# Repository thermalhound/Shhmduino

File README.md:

# SHHMduino
SHH&amp;M Arduino Clone

Files required to build the SHHMduino Arduino Clone

Initial upload on 22/01/2016 Rev A - UNTESTED

Update 5/7/2022 - Project no longer supported

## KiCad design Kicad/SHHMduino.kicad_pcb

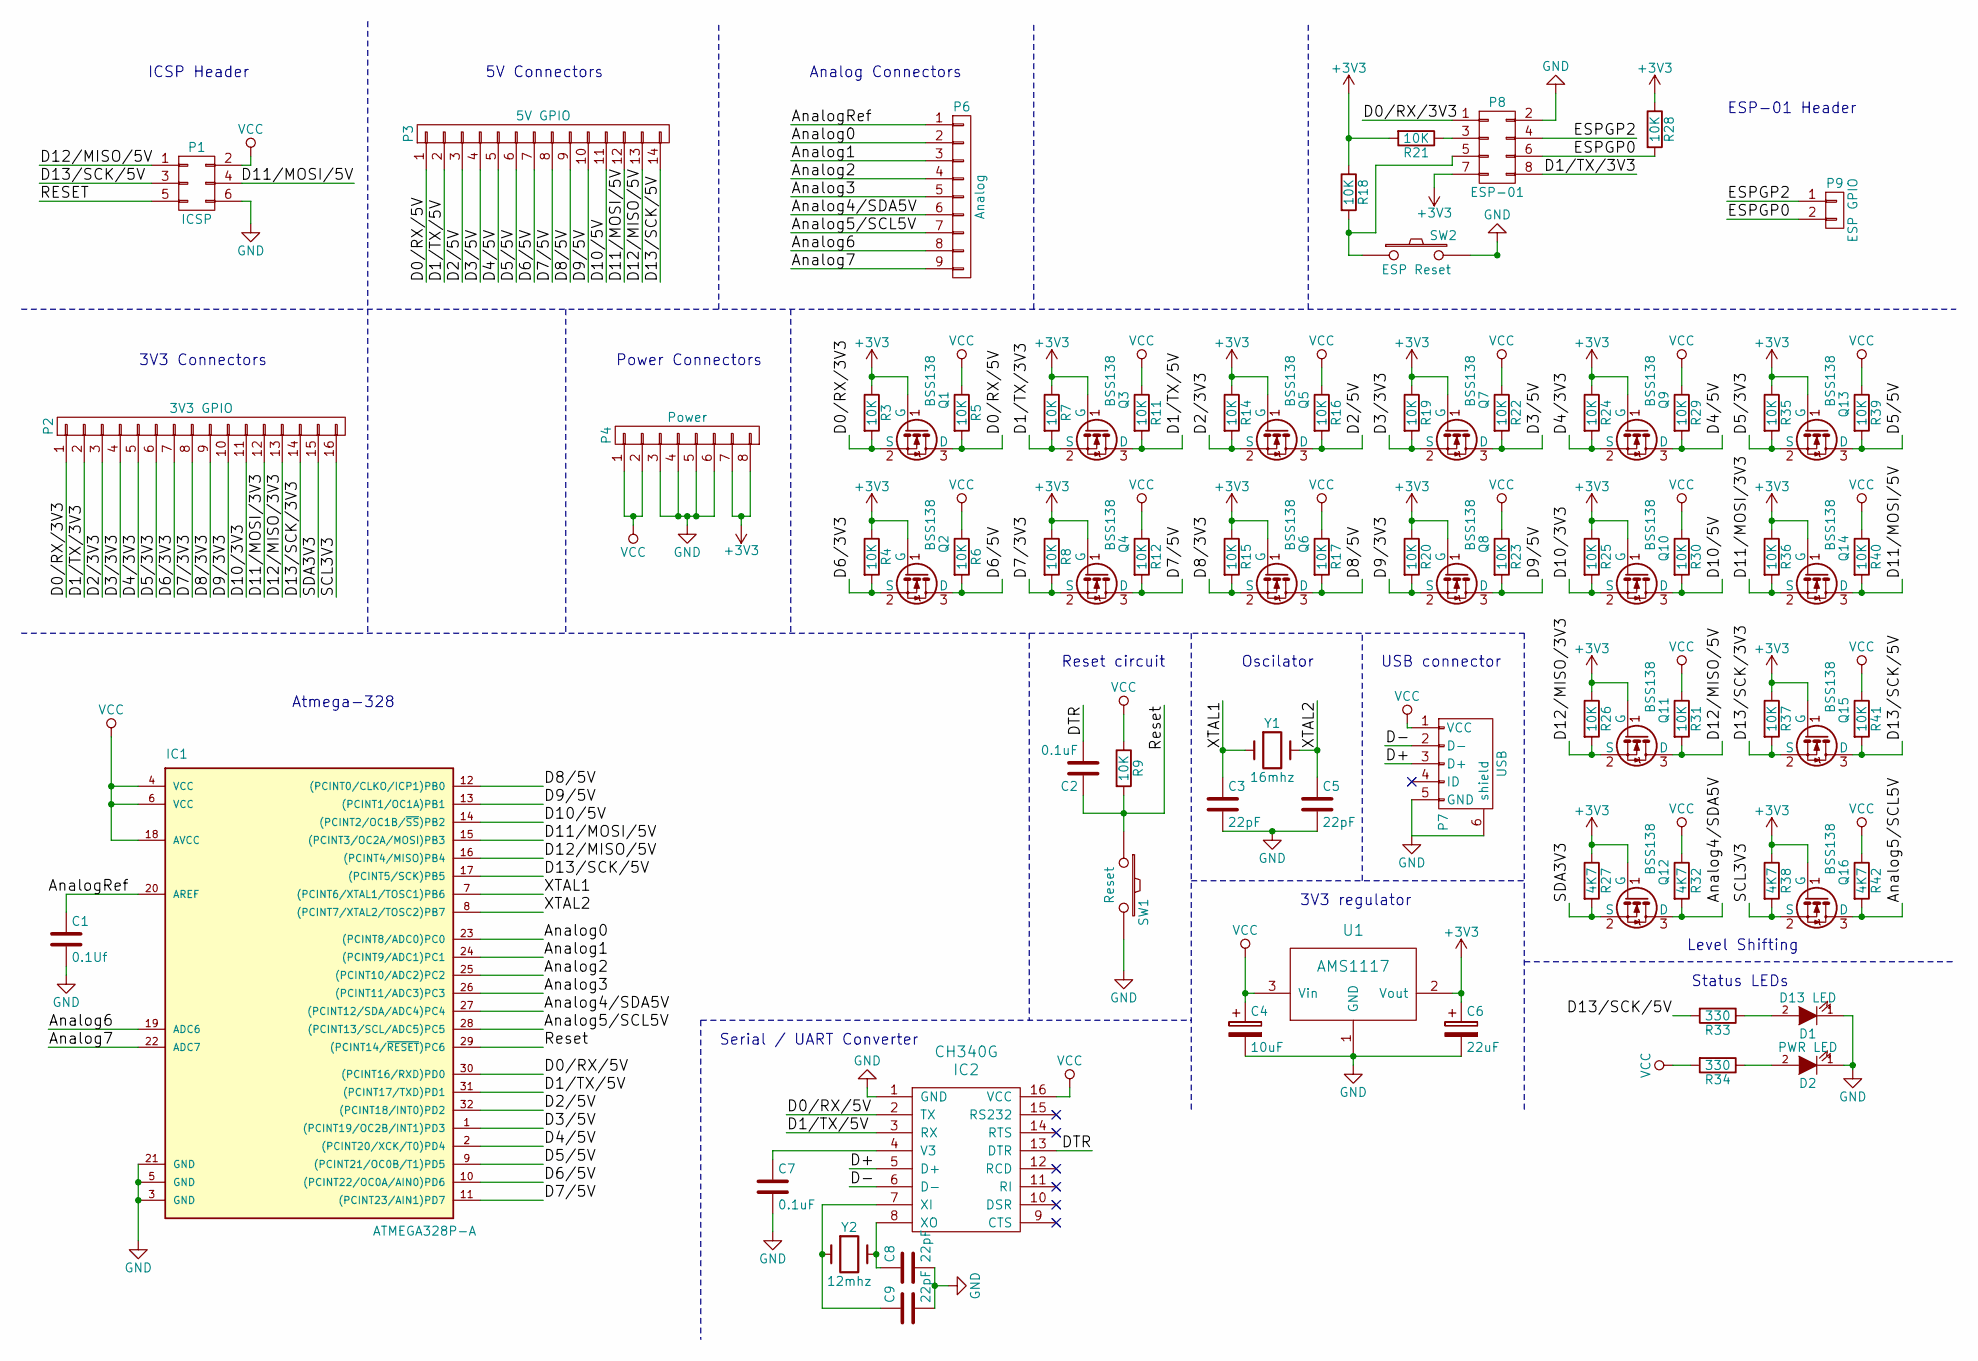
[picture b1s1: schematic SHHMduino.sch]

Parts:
C1: 0.1Uf; C_0805_HandSoldering
C2, C7: 0.1uF; C_0805_HandSoldering
C3, C5, C8, C9: 22pF; C_0805_HandSoldering
C4: 10uF; TantalC_SizeA_EIA-3216_HandSoldering
C6: 22uF; TantalC_SizeB_EIA-3528_HandSoldering
D1: D13 LED; LED-1206
D2: PWR LED; LED-1206
IC1: ATMEGA328P-A; TQFP-32_7x7mm_Pitch0.8mm
IC2: CH340G; -SOP16
P1: ICSP; Socket_Strip_Straight_2x03
P2: 3V3 GPIO; Socket_Strip_Straight_1x16
P3: 5V GPIO; Socket_Strip_Straight_1x14
P4: Power; Socket_Strip_Straight_1x08
P6: Analog; Socket_Strip_Straight_1x09
P7: USB; USB_Micro-B
P8: ESP-01; Socket_Strip_Straight_2x04
P9: ESP GPIO; Socket_Strip_Straight_1x02
Q1, Q2, Q3, Q4, Q5, Q6, Q7, Q8, Q9, Q10, Q11, Q12, Q13, Q14, Q15, Q16: BSS138; SOT-23_Handsoldering
R3, R4, R5, R6, R7, R8, R9, R11, R12, R14, R15, R16, R17, R18, R19, R20, R21, R22, R23, R24, R25, R26, R28, R29, R30, R31, R35, R36, R37, R39, R40, R41: 10K; R_0805_HandSoldering
R27, R32, R38, R42: 4K7; R_0805_HandSoldering
R33, R34: 330; R_0805_HandSoldering
SW1: Reset; SW_SPST_FSMSM
SW2: ESP Reset; SW_SPST_FSMSM
U1: AMS1117; SOT-223
Y1: 16mhz; Crystal_HC49-SD_SMD
Y2: 12mhz; Crystal_HC49-SD_SMD

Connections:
+3V3: C6.1, P4.7, P4.8, P8.7, Q1.1 (G), Q2.1 (G), Q3.1 (G), Q4.1 (G), Q5.1 (G), Q6.1 (G), Q7.1 (G), Q8.1 (G), Q9.1 (G), Q10.1 (G), Q11.1 (G), Q12.1 (G), Q13.1 (G), Q14.1 (G), Q15.1 (G), Q16.1 (G), R3.1, R4.1, R7.1, R8.1, R14.1, R15.1, R18.1, R19.1, R20.1, R21.2, R24.1, R25.1, R26.1, R27.1, R28.1, R35.1, R36.1, R37.1, R38.1, U1.2 (Vout)
/Analog0: IC1.23 ((PCINT8/ADC0)PC0), P6.2
/Analog1: IC1.24 ((PCINT9/ADC1)PC1), P6.3
/Analog2: IC1.25 ((PCINT10/ADC2)PC2), P6.4
/Analog3: IC1.26 ((PCINT11/ADC3)PC3), P6.5
/Analog4/SDA5V: IC1.27 ((PCINT12/SDA/ADC4)PC4), P6.6, Q12.3 (D), R32.2
/Analog5/SCL5V: IC1.28 ((PCINT13/SCL/ADC5)PC5), P6.7, Q16.3 (D), R42.2
/Analog6: IC1.19 (ADC6), P6.8
/Analog7: IC1.22 (ADC7), P6.9
/AnalogRef: C1.1, IC1.20 (AREF), P6.1
/D0/RX/3V3: P2.1, P8.1, Q1.2 (S), R3.2
/D0/RX/5V: IC1.30 ((PCINT16/RXD)PD0), IC2.2 (TX), P3.1, Q1.3 (D), R5.2
/D1/TX/3V3: P2.2, P8.8, Q3.2 (S), R7.2
/D1/TX/5V: IC1.31 ((PCINT17/TXD)PD1), IC2.3 (RX), P3.2, Q3.3 (D), R11.2
/D2/3V3: P2.3, Q5.2 (S), R14.2
/D2/5V: IC1.32 ((PCINT18/INT0)PD2), P3.3, Q5.3 (D), R16.2
/D3/3V3: P2.4, Q7.2 (S), R19.2
/D3/5V: IC1.1 ((PCINT19/OC2B/INT1)PD3), P3.4, Q7.3 (D), R22.2
/D4/3V3: P2.5, Q9.2 (S), R24.2
/D4/5V: IC1.2 ((PCINT20/XCK/T0)PD4), P3.5, Q9.3 (D), R29.2
/D5/3V3: P2.6, Q13.2 (S), R35.2
/D5/5V: IC1.9 ((PCINT21/OC0B/T1)PD5), P3.6, Q13.3 (D), R39.2
/D6/3V3: P2.7, Q2.2 (S), R4.2
/D6/5V: IC1.10 ((PCINT22/OC0A/AIN0)PD6), P3.7, Q2.3 (D), R6.2
/D7/3V3: P2.8, Q4.2 (S), R8.2
/D7/5V: IC1.11 ((PCINT23/AIN1)PD7), P3.8, Q4.3 (D), R12.2
/D8/3V3: P2.9, Q6.2 (S), R15.2
/D8/5V: IC1.12 ((PCINT0/CLKO/ICP1)PB0), P3.9, Q6.3 (D), R17.2
/D9/3V3: P2.10, Q8.2 (S), R20.2
/D9/5V: IC1.13 ((PCINT1/OC1A)PB1), P3.10, Q8.3 (D), R23.2
/D10/3V3: P2.11, Q10.2 (S), R25.2
/D10/5V: IC1.14 ((PCINT2/OC1B/~SS~)PB2), P3.11, Q10.3 (D), R30.2
/D11/MOSI/3V3: P2.12, Q14.2 (S), R36.2
/D11/MOSI/5V: IC1.15 ((PCINT3/OC2A/MOSI)PB3), P1.4, P3.12, Q14.3 (D), R40.2
/D12/MISO/3V3: P2.13, Q11.2 (S), R26.2
/D12/MISO/5V: IC1.16 ((PCINT4/MISO)PB4), P1.1, P3.13, Q11.3 (D), R31.2
/D13/SCK/3V3: P2.14, Q15.2 (S), R37.2
/D13/SCK/5V: IC1.17 ((PCINT5/SCK)PB5), P1.3, P3.14, Q15.3 (D), R33.2, R41.2
/D+: IC2.5 (D+), P7.3 (D+)
/D-: IC2.6 (D-), P7.2 (D-)
/DTR: C2.2, IC2.13 (DTR)
/ESPGP0: P8.6, P9.2, R28.2
/ESPGP2: P8.4, P9.1
/RESET: C2.1, IC1.29 ((PCINT14/~RESET~)PC6), P1.5, R9.2, SW1.1
/SCL3V3: P2.16, Q16.2 (S), R38.2
/SDA3V3: P2.15, Q12.2 (S), R27.2
/XTAL1: C3.1, IC1.7 ((PCINT6/XTAL1/TOSC1)PB6), Y1.1
/XTAL2: C5.1, IC1.8 ((PCINT7/XTAL2/TOSC2)PB7), Y1.2
GND: C1.2, C3.2, C4.2, C5.2, C6.2, C7.2, C8.2, C9.2, D1.1 (K), D2.1 (K), IC1.3 (GND), IC1.5 (GND), IC1.21 (GND), IC2.1 (GND), P1.6, P4.3, P4.4, P4.5, P4.6, P7.5 (GND), P7.6 (shield), P8.2, SW1.2, SW2.2, U1.1 (GND)
unnamed: C7.1, IC2.4 (V3)
unnamed: C8.1, IC2.8 (XO), Y2.2
unnamed: C9.1, IC2.7 (XI), Y2.1
unnamed: D1.2 (A), R33.1
unnamed: D2.2 (A), R34.1
unnamed: P8.3, R21.1
unnamed: P8.5, R18.2, SW2.1
VCC: C4.1, IC1.4 (VCC), IC1.6 (VCC), IC1.18 (AVCC), IC2.16 (VCC), P1.2, P4.1, P4.2, P7.1 (VCC), R5.1, R6.1, R9.1, R11.1, R12.1, R16.1, R17.1, R22.1, R23.1, R29.1, R30.1, R31.1, R32.1, R34.2, R39.1, R40.1, R41.1, R42.1, U1.3 (Vin)

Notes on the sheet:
ICSP Header
5V Connectors
Analog Connectors
Power Connectors
3V3 regulator
Level Shifting
3V3 Connectors
ESP-01 Header
Serial / UART Converter
USB connector
Status LEDs
Reset circuit
Oscilator
Atmega-328

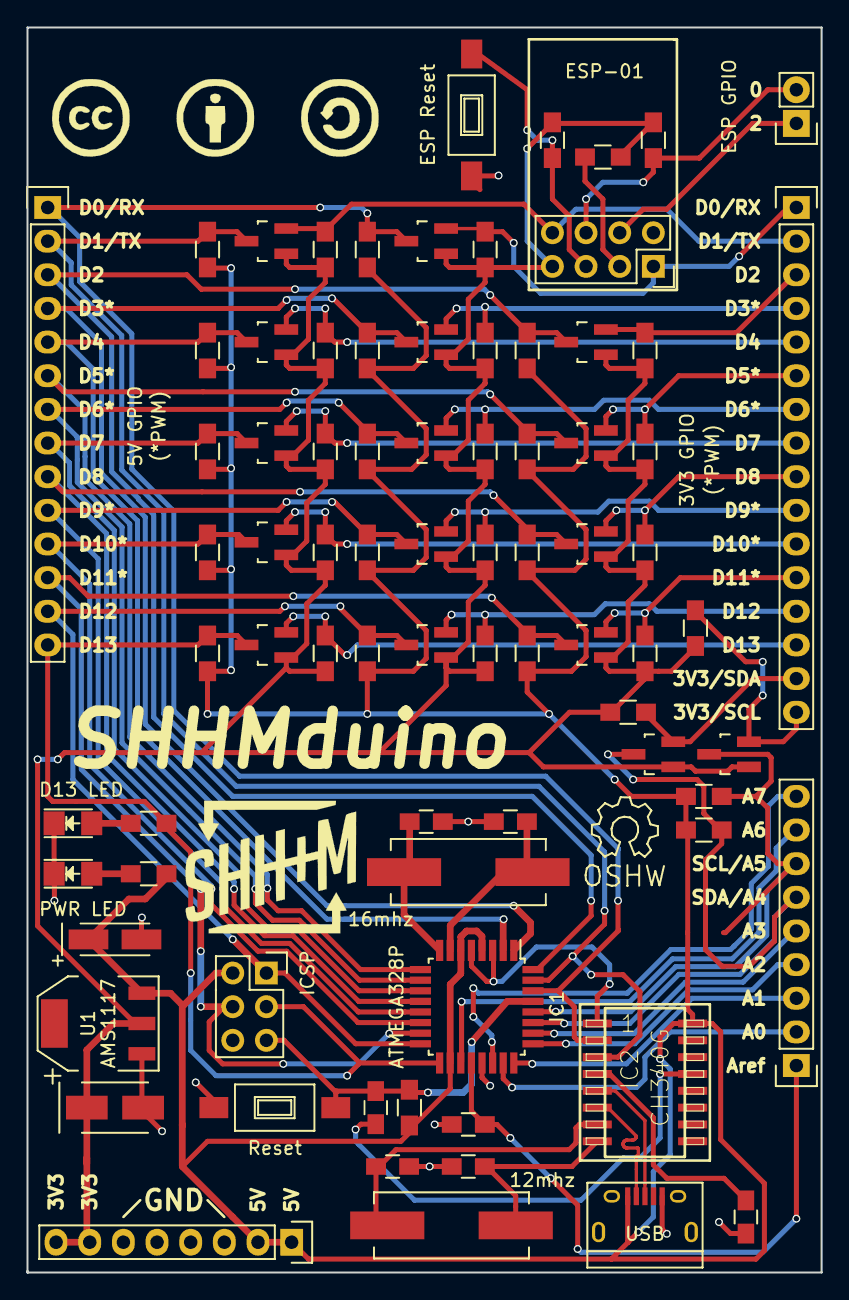
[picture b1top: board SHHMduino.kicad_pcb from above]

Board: 2 copper layers, 59.9 x 94.0 mm, 80 parts (0 on the bottom side), 57 nets.

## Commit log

2016-01-22 Initial upload
    Initial upload of the Rev A kicad files and gerbers
2016-01-22 Organised file stricture
    Organised files into Rev A directory
2016-01-22 Update README.md
    Note added with upload date and untested status
2016-01-22 Rev A
    Rev A silkscreen added
2016-01-22 Spelling change
    SHHMduino
2016-01-23 Edge file changed
    Edge file changed from .gb1 to .gbr for compatibility with DirtyPCB
    uploader
2022-07-05 2022 update
2022-07-05 Final Update

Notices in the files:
Kicad/SHHMduino.kicad_pcb:
licensed under a Creative Commons
Attribution-ShareAlike 4.0 International License
Kicad/SHHMduino.sch:
SHHMduino is licensed under a Creative Commons Attribution-ShareAlike
